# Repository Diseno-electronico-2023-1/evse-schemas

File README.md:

# evse-schemas

Cada grupo crea una rama para su PCB, cuando acaben hacen merge a la rama

Para crear una rama:

git checkout -b branch-name

Donde branch-name es el nombre de la rama Ej: Potencia

Una vez que estan en la nueva rama pueden subir sus cambios con:

git add .

git commit -m "Descripción de sus cambios"

git push -u origin branch-name

## Table of Contents
- [Conector](#conector)
- [Control Pilot](#controlPilot)

## CONECTOR
### Pruebas
#### Tension
Para esta prueba se realiza un montaje en paralelo entre una linea y neutro del conector con una fuente de tensión en AC, Como se observa en el siguiente montaje.

Se realiza la respectiva verificación de la tensión a la que estará expuesto el conector y se realizan distintas pruebas con diferentes valores de voltaje obteniendo los siguientes resultados.

#### Corriente
En esta prueba se conecto en serie una fuente de corriente como se muestra en la siguiente figura.

Se inicio la medicion con 5 A y posteriormente se aumento a los 15 A que están propuestos para el cargador y con la ayuda de una pinza amperimétrica y un osciloscopio se observaron las corrientes suministradas en una escala de 10mV por cada amperio.

#### Aislamiento
Para determinar la resistencia de aislamiento del conector se utiliza un medidor de resistencia de aislamiento, con los cables aislados entre si se conectan a una linea y al neutro del conector como se observa el montaje en la siguiente figura. La resistencia obtenida fue de 319 Gohm. 

Comparando este valor con el dado comercialmente se obtiene una resistencia considerablemente mayor a la descrita en el manual.

<div align="center">

Votaje [RMS]  | Corriente [A] | Aislamiento [Gomh]
------------- | ------------- | -------------
121  | 5  | 319
383  | 15 
447  | 16
</div>

## CONTROL PILOT
El circuito piloto de control es el principal medio de control para garantizar un funcionamiento correcto al conectar un EV/PHEV al EVSE. La señal piloto es el método clave a través del cual un EVSE compatible con J1772 se comunica con un vehículo. La señal piloto se basa en una señal PWM de ±12 V y 1 kHz que se transmite a un vehículo a través del cable de carga. El vehículo puede entonces responder colocando diversas cargas en la línea, afectando a su tensión, que mide el EVSE.
El protocolo de señalización ha sido diseñado para la siguiente secuencia de carga.

- El equipo de alimentación señala la presencia de alimentación de entrada de CA
- El vehículo detecta el enchufe mediante un circuito de proximidad (de este modo, el vehículo puede evitar alejarse mientras está conectado) y puede detectar cuando se pulsa el pestillo para preparar la extracción del enchufe.

Comienzan las funciones del piloto de control (CP)

- El equipo de alimentación detecta el vehículo eléctrico enchufable (PEV)
- El equipo de suministro indica al PEV que está preparado para suministrar corriente
- Se determinan las necesidades de ventilación del PEV
- el equipo de alimentación suministra corriente al PEV
- El PEV ordena el flujo de energía
- El PEV y el equipo de alimentación supervisan continuamente la continuidad de la toma de tierra de seguridad
- La carga continúa según lo determinado por el PEV
- La carga puede interrumpirse desconectando el enchufe del vehículo

Esta seccion esta basado en la plantilla [Conector](https://github.com/Diseno-electronico-2023-1/evse-schemas/tree/Conector/Conector "Conector")

### Control Pilot - simulación
Este apartado tiene como carpeta principal [Simulación](https://github.com/Diseno-electronico-2023-1/evse-schemas/tree/Conector/Conector/Simulacion)

#### Table SAE J1772 - PILOT SIGNAL
<div align="center">
                    
Designación del estado del vehículo  |Voltaje (VDC nominal) | Descripción del estado del vehículo
------------- | ------------- | -------------
Estado A  | 12 | Vehículo no conectado
Estado B  | 9 | Vehículo conectado / no está listo para aceptar energía
Estado C  | 6 | Vehículo conectado / listo para aceptar energía / no se requiere ventilación en el área de carga interna
Estado D  | 3 | Vehículo conectado / listo para aceptar energía /requiere ventilación en el área de carga interna
Estado E  | 0 | EVSE desconectado, poder de utilidad no disponible, u otro problema de EVSE
Estado F  | -12 | EVSE no disponible, u otro problema de EVSE
</div>

1. El EVSE pone 12V en el cable piloto. Esta transmisión señala al vehículo cuando el enchufe está conectado.
2. Cuando se conecta el enchufe, el vehículo coloca una carga de 2,74 kΩ en la línea piloto, lo que disminuye la tensión a 9 V.
3. La EVSE pasa al estado B, donde activa el PWM, que indica al vehículo cuánta corriente puede consumir. El EVSE también cierra los relés, proporcionando energía al vehículo.
4. El vehículo comienza a consumir energía y cambia a la carga de 822-Ω, que baja la tensión a 6 V, señalando al EVSE que la carga ha comenzado.
5. La mayoría de los vehículos siguen consumiendo pequeñas cantidades de energía en el estado C, incluso cuando están completamente cargados, por lo que el proceso de carga finaliza desenchufando el cable, lo que devuelve la tensión a 12 V. El EVSE mide este proceso y cierra los relés y vuelve al estado A.

#### J1772 Ciclo de trabajo

El ciclo de trabajo de las señales piloto comunica el límite de corriente que el EVSE es capaz de suministrar al vehículo; el vehículo puede entonces utilizar hasta esa cantidad de corriente para su circuito de carga. Este límite de corriente viene determinada principalmente por los componentes electromecánicos de la EVSE, como conductores, relés contactores y la conexión de servicio. La relación entre el ciclo de trabajo y la corriente se define mediante dos ecuaciones diferentes en función del rango de corriente especificado.

Rango de corriente especificado; para un servicio de 6 a 51 A, es:
Duty Cycle = Amps / 0.6

<div align="center">

AMPS  | DUTY CYCLE
------------- | -------------
5  | 8.3%
15  | 25% 
30  | 50%
40  | 66.6%
65  | 90%
80  | 96%
</div>

### Control Pilot - PCB
Esta subseccion esta basado en la plantilla [PCB](https://github.com/Diseno-electronico-2023-1/evse-schemas/tree/Conector/Conector/ControlPilotPCB-backups)

<p align="center">

</p>

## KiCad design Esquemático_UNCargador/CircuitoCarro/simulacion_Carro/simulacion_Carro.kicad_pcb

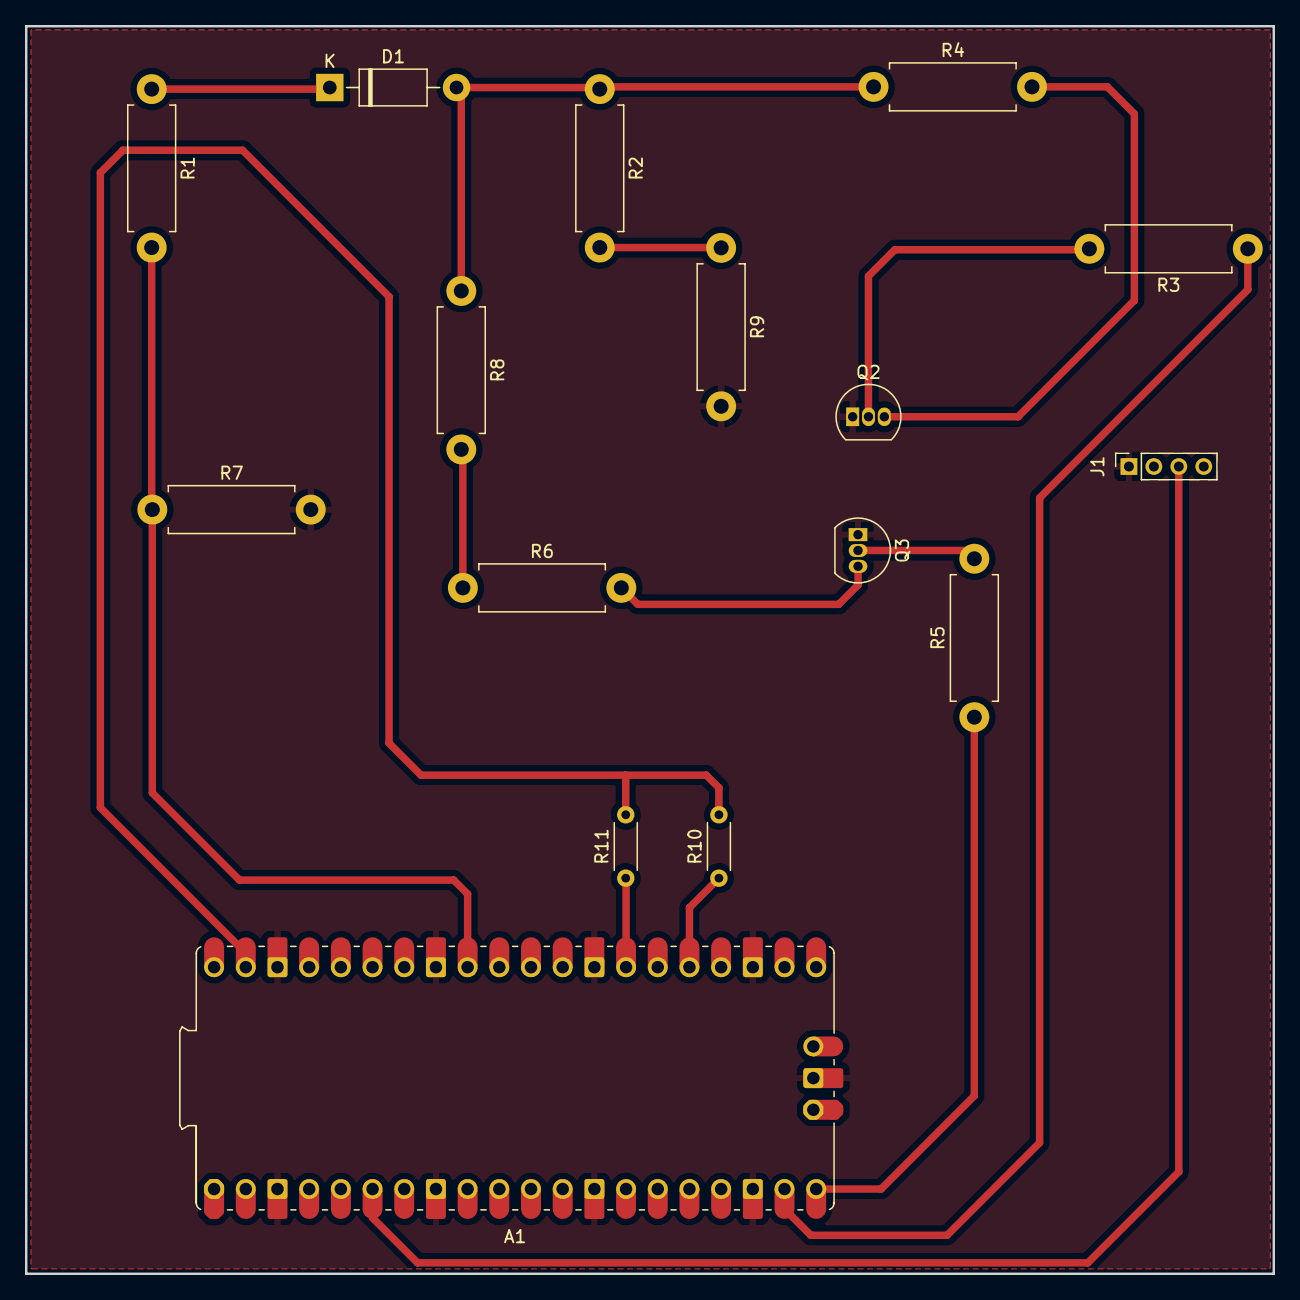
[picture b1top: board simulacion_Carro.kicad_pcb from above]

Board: 2 copper layers, 100.0 x 100.0 mm, 16 parts (0 on the bottom side), 16 nets.

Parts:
A1: RaspberryPi-Pico; Raspberry_Pi_Pico_SMT_THT
D1: 1N4004; D_DO-41_SOD81_P10.16mm_Horizontal
J1: Conn_01x04_Pin; PinSocket_1x04_P2.00mm_Vertical
Q2, Q3: 2N2222; TO-92_Inline
R1: 90k; R_Axial_DIN0411_L9.9mm_D3.6mm_P12.70mm_Horizontal
R2: 2.7k; R_Axial_DIN0411_L9.9mm_D3.6mm_P12.70mm_Horizontal
R3, R5: 1k; R_Axial_DIN0411_L9.9mm_D3.6mm_P12.70mm_Horizontal
R4: 330; R_Axial_DIN0411_L9.9mm_D3.6mm_P12.70mm_Horizontal
R6: 1.2k; R_Axial_DIN0411_L9.9mm_D3.6mm_P12.70mm_Horizontal
R7: 10k; R_Axial_DIN0411_L9.9mm_D3.6mm_P12.70mm_Horizontal
R8: 100; R_Axial_DIN0411_L9.9mm_D3.6mm_P12.70mm_Horizontal
R9: 39; R_Axial_DIN0411_L9.9mm_D3.6mm_P12.70mm_Horizontal
R10, R11: R; R_Axial_DIN0204_L3.6mm_D1.6mm_P5.08mm_Horizontal

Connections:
+5V: A1.39 (VSYS), R10.2, R11.2
/micro/pilot_micro: A1.32 (GPIO27_ADC1), R1.2, R7.1
/micro/pwm1: A1.19 (GPIO14), R3.1
/micro/pwm2: A1.20 (GPIO15), R5.1
GND: A1.3 (GND), A1.8 (GND), A1.13 (GND), A1.18 (GND), A1.23 (GND), A1.28 (GND), A1.33 (AGND), A1.38 (GND), A1.42 (SWGND), J1.1, Q2.1 (E), Q3.1 (E), R7.2, R9.2
unnamed: A1.25 (GPIO19), R10.1
unnamed: A1.27 (GPIO21), R11.1
unnamed: D1.1 (K), R1.1
unnamed: Q2.2 (B), R3.2
unnamed: Q2.3 (C), R4.2
unnamed: Q3.2 (B), R5.2
unnamed: Q3.3 (C), R6.2
unnamed: R2.2, R9.1
unnamed: R6.1, R8.2
SDA: A1.6 (GPIO4), J1.3
pilot_in_carg: D1.2 (A), R2.1, R4.1, R8.1

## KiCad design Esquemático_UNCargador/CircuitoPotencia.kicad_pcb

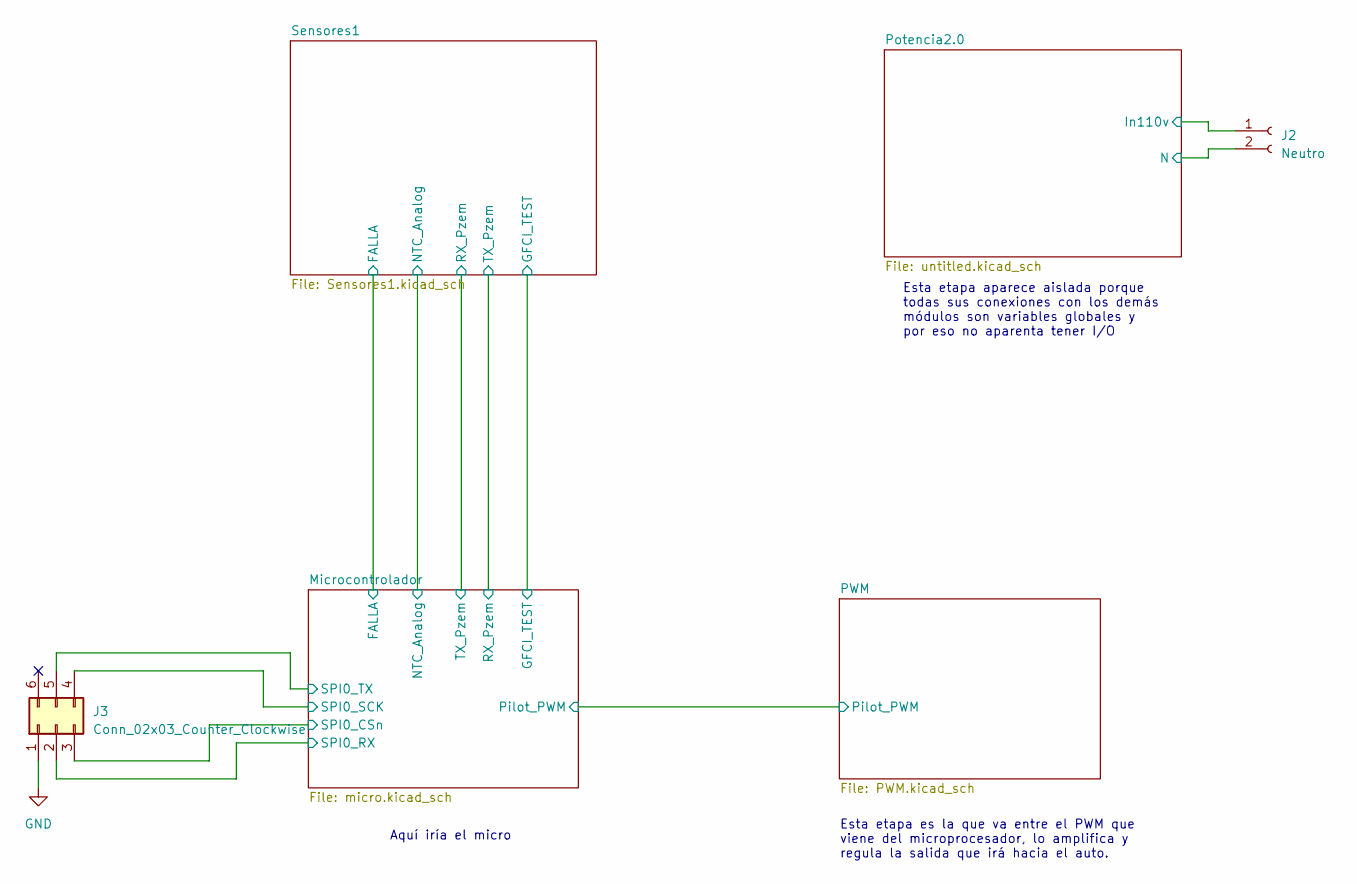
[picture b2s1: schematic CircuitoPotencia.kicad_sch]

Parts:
J2: Neutro; TerminalBlock_Wuerth_691311400102_P7.62mm
J3: Conn_02x03_Counter_Clockwise; IDC-Header_2x05_P2.54mm_Vertical

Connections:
/Microcontrolador/SPI0_CSn: J3.3; also elsewhere on the board
/Microcontrolador/SPI0_RX: J3.2; also elsewhere on the board
/Microcontrolador/SPI0_SCK: J3.4; also elsewhere on the board
/Microcontrolador/SPI0_TX: J3.5; also elsewhere on the board
unnamed 21: J2.2; also elsewhere on the board
unnamed 22: J2.1; also elsewhere on the board

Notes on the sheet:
Aquí iría el micro
Esta etapa es la que va entre el PWM que viene del microprocesador, lo amplifica y regula la salida que irá hacia el auto.
Esta etapa aparece aislada porque todas sus conexiones con los demás módulos son variables globales y por eso no aparenta tener I/O

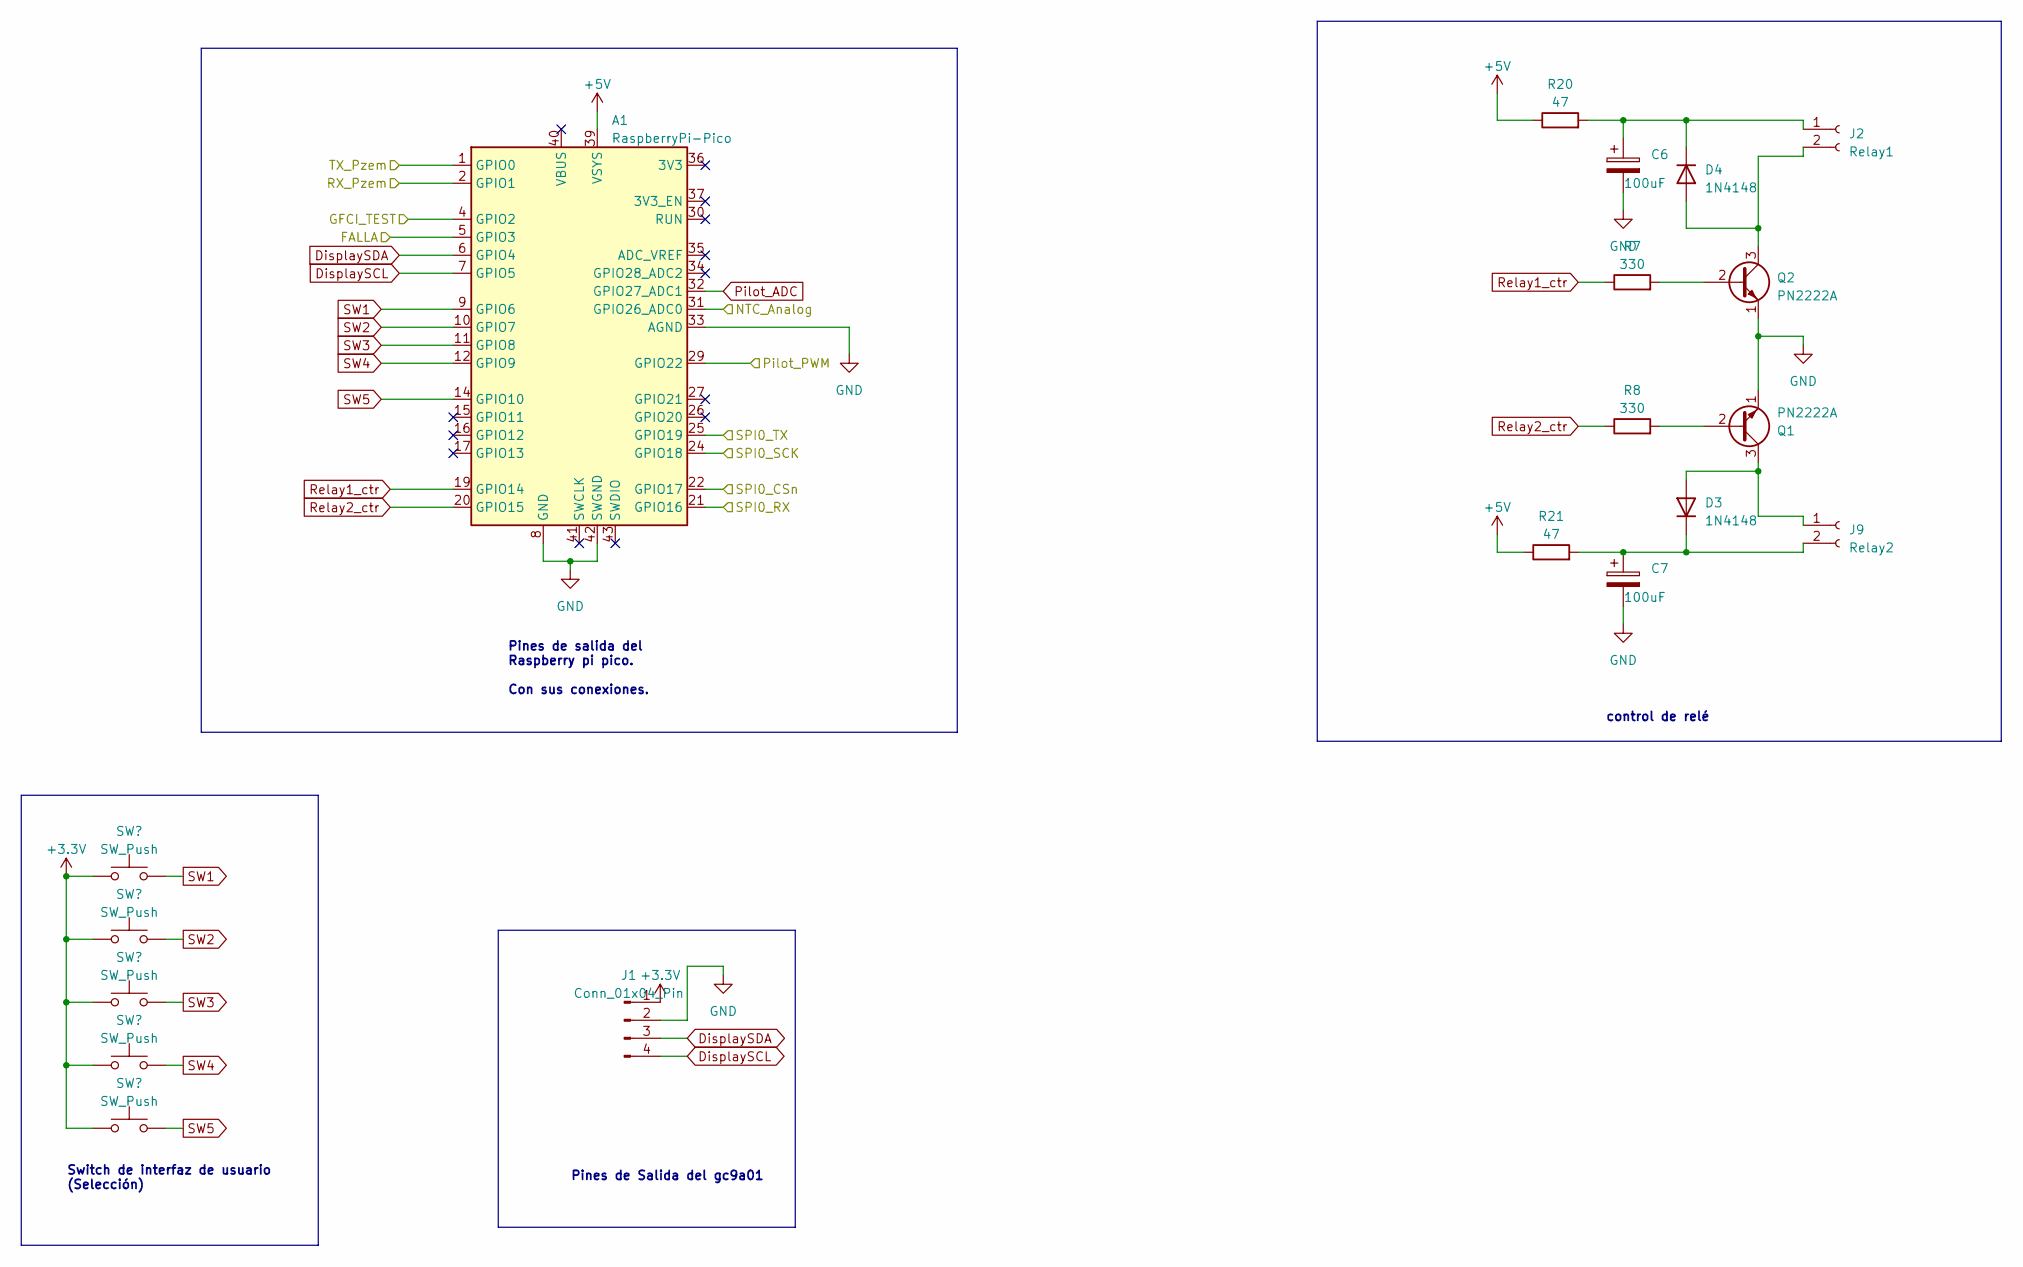
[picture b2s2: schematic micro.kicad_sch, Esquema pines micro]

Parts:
A1: RaspberryPi-Pico; Raspberry_Pi_Pico_SMT_THT
C6, C7: 100uF; CP_Radial_D8.0mm_P3.50mm
D3, D4: 1N4148; D_DO-35_SOD27_P7.62mm_Horizontal
J1: Conn_01x04_Pin; PinHeader_1x04_P2.54mm_Vertical
J2: Relay1; Molex_KK-254_AE-6410-02A_1x02_P2.54mm_Vertical
J9: Relay2; Molex_KK-254_AE-6410-02A_1x02_P2.54mm_Vertical
Q1, Q2: PN2222A; TO-92_Inline
R7, R8: 330; R_Axial_DIN0207_L6.3mm_D2.5mm_P10.16mm_Horizontal
R20, R21: 47; R_Axial_DIN0207_L6.3mm_D2.5mm_P10.16mm_Horizontal
SW1, SW2, SW3, SW4, SW5: SW_Push; PinHeader_1x02_P2.54mm_Vertical

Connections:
+3.3V: J1.1, SW1.1, SW2.1, SW3.1, SW4.1, SW5.1; also elsewhere on the board
+5V: A1.39 (VSYS), R20.1, R21.1; also elsewhere on the board
/Microcontrolador/FALLA: A1.5 (GPIO3); also elsewhere on the board
/Microcontrolador/GFCI_TEST: A1.4 (GPIO2); also elsewhere on the board
/Microcontrolador/NTC_Analog: A1.31 (GPIO26_ADC0); also elsewhere on the board
/Microcontrolador/Pilot_PWM: A1.29 (GPIO22); also elsewhere on the board
/Microcontrolador/RX_Pzem: A1.2 (GPIO1); also elsewhere on the board
/Microcontrolador/SPI0_CSn: A1.22 (GPIO17); also elsewhere on the board
/Microcontrolador/SPI0_RX: A1.21 (GPIO16); also elsewhere on the board
/Microcontrolador/SPI0_SCK: A1.24 (GPIO18); also elsewhere on the board
/Microcontrolador/SPI0_TX: A1.25 (GPIO19); also elsewhere on the board
/Microcontrolador/TX_Pzem: A1.1 (GPIO0); also elsewhere on the board
DisplaySCL: A1.7 (GPIO5), J1.4
DisplaySDA: A1.6 (GPIO4), J1.3
unnamed: D3.2 (A), J9.1, Q1.3 (C)
unnamed: C7.1, D3.1 (K), J9.2, R21.2
unnamed: D4.2 (A), J2.2, Q2.3 (C)
unnamed: C6.1, D4.1 (K), J2.1, R20.2
unnamed: Q1.2 (B), R8.2
unnamed: Q2.2 (B), R7.2
Pilot_ADC: A1.32 (GPIO27_ADC1); also elsewhere on the board
Relay1_ctr: A1.19 (GPIO14), R7.1
Relay2_ctr: A1.20 (GPIO15), R8.1
SW1: A1.9 (GPIO6), SW1.2
SW2: A1.10 (GPIO7), SW2.2
SW3: A1.11 (GPIO8), SW3.2
SW4: A1.12 (GPIO9), SW4.2
SW5: A1.14 (GPIO10), SW5.2

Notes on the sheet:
Pines de salida del Raspberry pi pico. Con sus conexiones.
control de relé
Switch de interfaz de usuario (Selección)
Pines de Salida del gc9a01

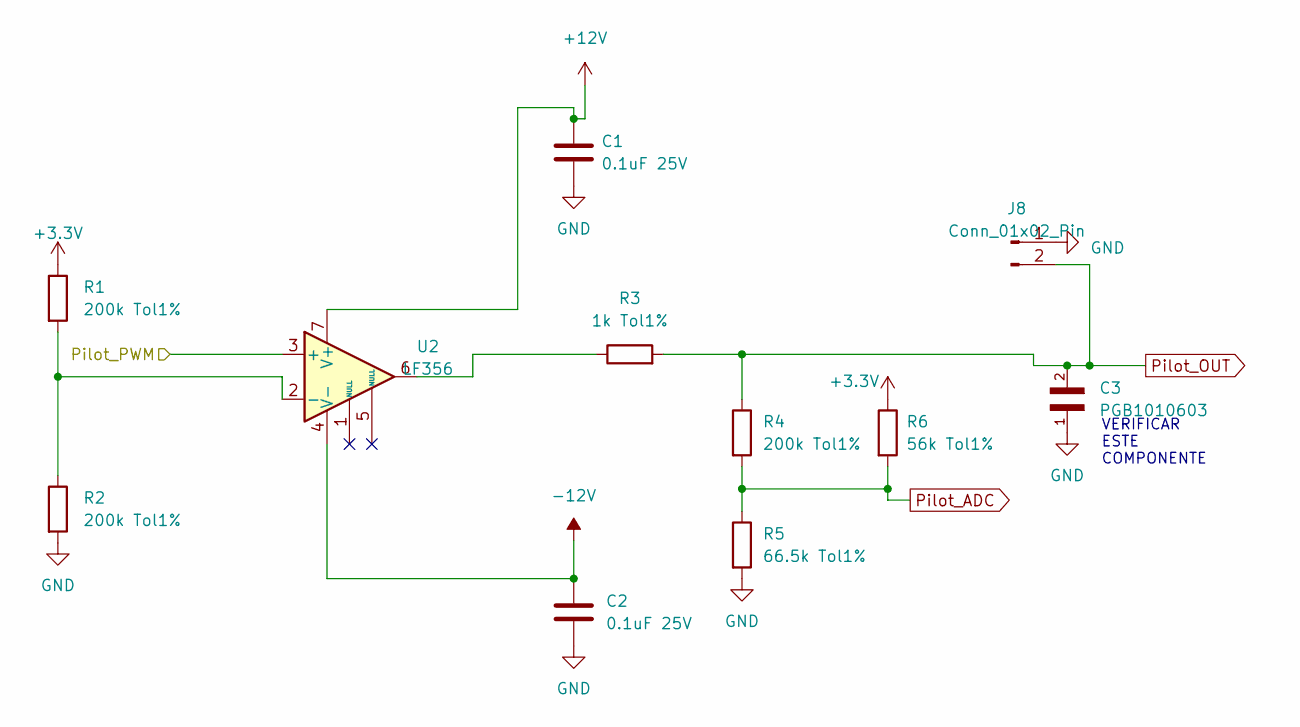
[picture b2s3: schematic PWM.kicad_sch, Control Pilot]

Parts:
C1, C2: 0.1uF 25V; CP_Radial_D4.0mm_P1.50mm
C3: PGB1010603; R_0603_1608Metric_Pad0.98x0.95mm_HandSolder
J8: Conn_01x02_Pin; TerminalBlock_Wuerth_691311400102_P7.62mm
R1, R2, R4: 200k Tol1%; R_Axial_DIN0204_L3.6mm_D1.6mm_P5.08mm_Horizontal
R3: 1k Tol1%; R_Axial_DIN0204_L3.6mm_D1.6mm_P5.08mm_Horizontal
R5: 66.5k Tol1%; R_Axial_DIN0204_L3.6mm_D1.6mm_P5.08mm_Horizontal
R6: 56k Tol1%; R_Axial_DIN0204_L3.6mm_D1.6mm_P5.08mm_Horizontal
U2: LF356; DIL08

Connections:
+3.3V: R1.1, R6.1; also elsewhere on the board
+12V: C1.1, U2.7 (V+); also elsewhere on the board
-12V: C2.1, U2.4 (V-); also elsewhere on the board
/Microcontrolador/Pilot_PWM: U2.3 (+); also elsewhere on the board
unnamed: R3.1, U2.6
unnamed: R1.2, R2.1, U2.2 (-)
Pilot_ADC: R4.2, R5.1, R6.2; also elsewhere on the board
Pilot_OUT: C3.2, J8.2, R3.2, R4.1

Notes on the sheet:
VERIFICAR ESTE COMPONENTE

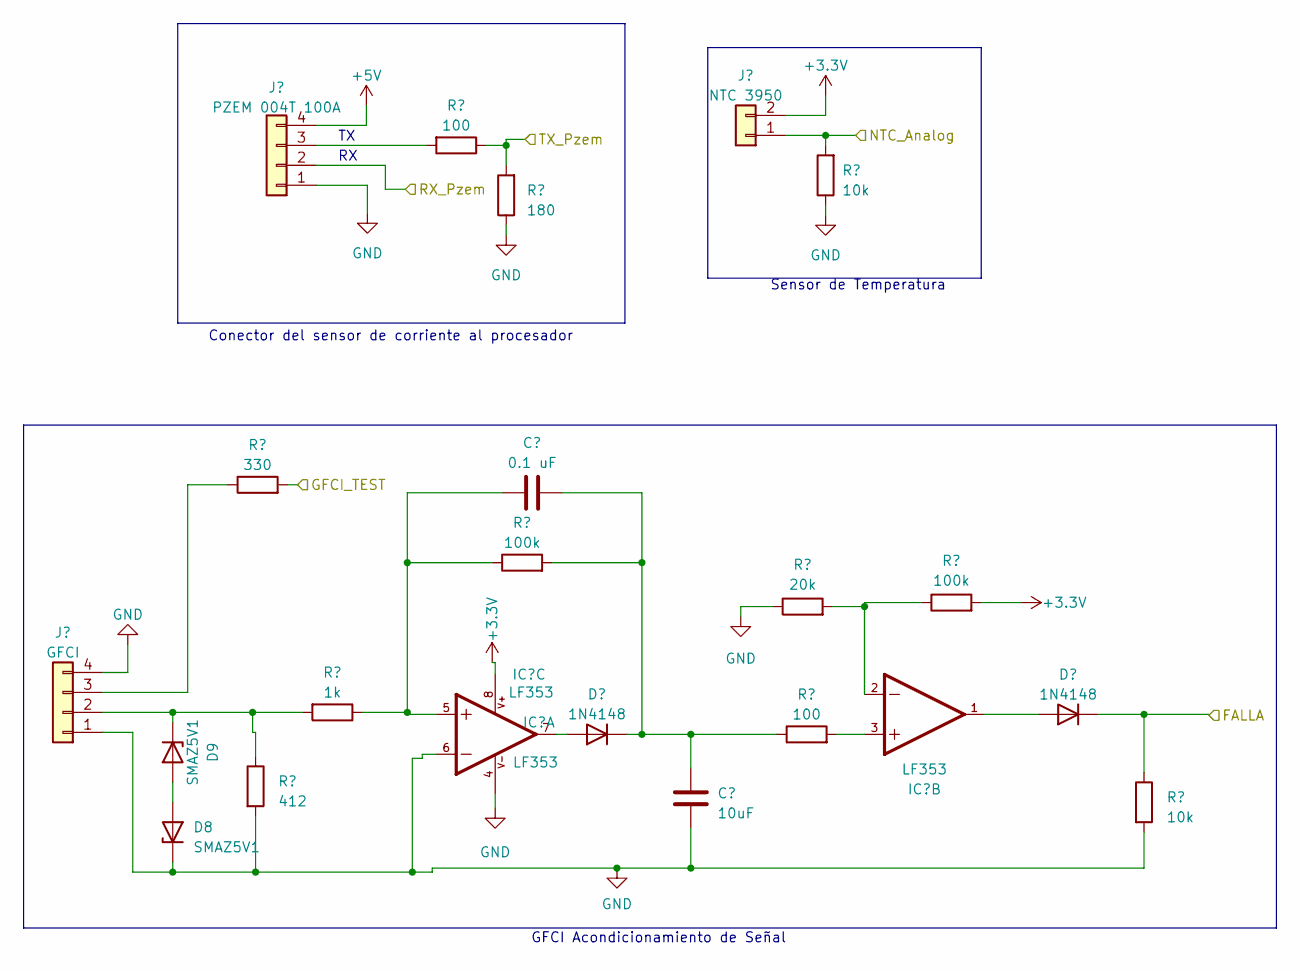
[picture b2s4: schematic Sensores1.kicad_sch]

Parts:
C4: 0.1 uF; C_0805_2012Metric_Pad1.18x1.45mm_HandSolder
C5: 10uF; C_0805_2012Metric_Pad1.18x1.45mm_HandSolder
D5, D6: 1N4148; D_DO-35_SOD27_P7.62mm_Horizontal
D8, D9: SMAZ5V1; DO-214AC
IC1: LF353; DIL08
J4: GFCI; JST_EH_B4B-EH-A_1x04_P2.50mm_Vertical
J5: PZEM 004T 100A; PZEM
J6: NTC 3950; JST_EH_B2B-EH-A_1x02_P2.50mm_Vertical
R9: 412; R_1206_3216Metric_Pad1.30x1.75mm_HandSolder
R10: 330; R_1206_3216Metric_Pad1.30x1.75mm_HandSolder
R11: 1k; R_1206_3216Metric_Pad1.30x1.75mm_HandSolder
R12, R16: 100; R_1206_3216Metric_Pad1.30x1.75mm_HandSolder
R13: 180; R_1206_3216Metric_Pad1.30x1.75mm_HandSolder
R14, R18: 100k; R_1206_3216Metric_Pad1.30x1.75mm_HandSolder
R15: 20k; R_1206_3216Metric_Pad1.30x1.75mm_HandSolder
R17, R19: 10k; R_1206_3216Metric_Pad1.30x1.75mm_HandSolder

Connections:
+3.3V: IC1.8, J6.2, R18.2; also elsewhere on the board
+5V: J5.4; also elsewhere on the board
/Microcontrolador/FALLA: D6.1 (K), R19.1; also elsewhere on the board
/Microcontrolador/GFCI_TEST: R10.2; also elsewhere on the board
/Microcontrolador/NTC_Analog: J6.1, R17.2; also elsewhere on the board
/Microcontrolador/RX_Pzem: R12.1, R13.2; also elsewhere on the board
/Microcontrolador/TX_Pzem: J5.2; also elsewhere on the board
unnamed: C4.1, IC1.5, R11.1, R14.1
unnamed: D5.2 (A), IC1.7
unnamed: C4.2, C5.1, D5.1 (K), R14.2, R16.1
unnamed: D6.2 (A), IC1.1
unnamed: D8.2 (A), D9.2 (A)
unnamed: D9.1 (K), J4.2, R9.1, R11.2
unnamed: IC1.2, R15.2, R18.1
unnamed: IC1.3, R16.2
unnamed: J4.3, R10.1
unnamed: J5.3, R12.2

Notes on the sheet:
Conector del sensor de corriente al procesador
GFCI Acondicionamiento de Señal
Sensor de Temperatura

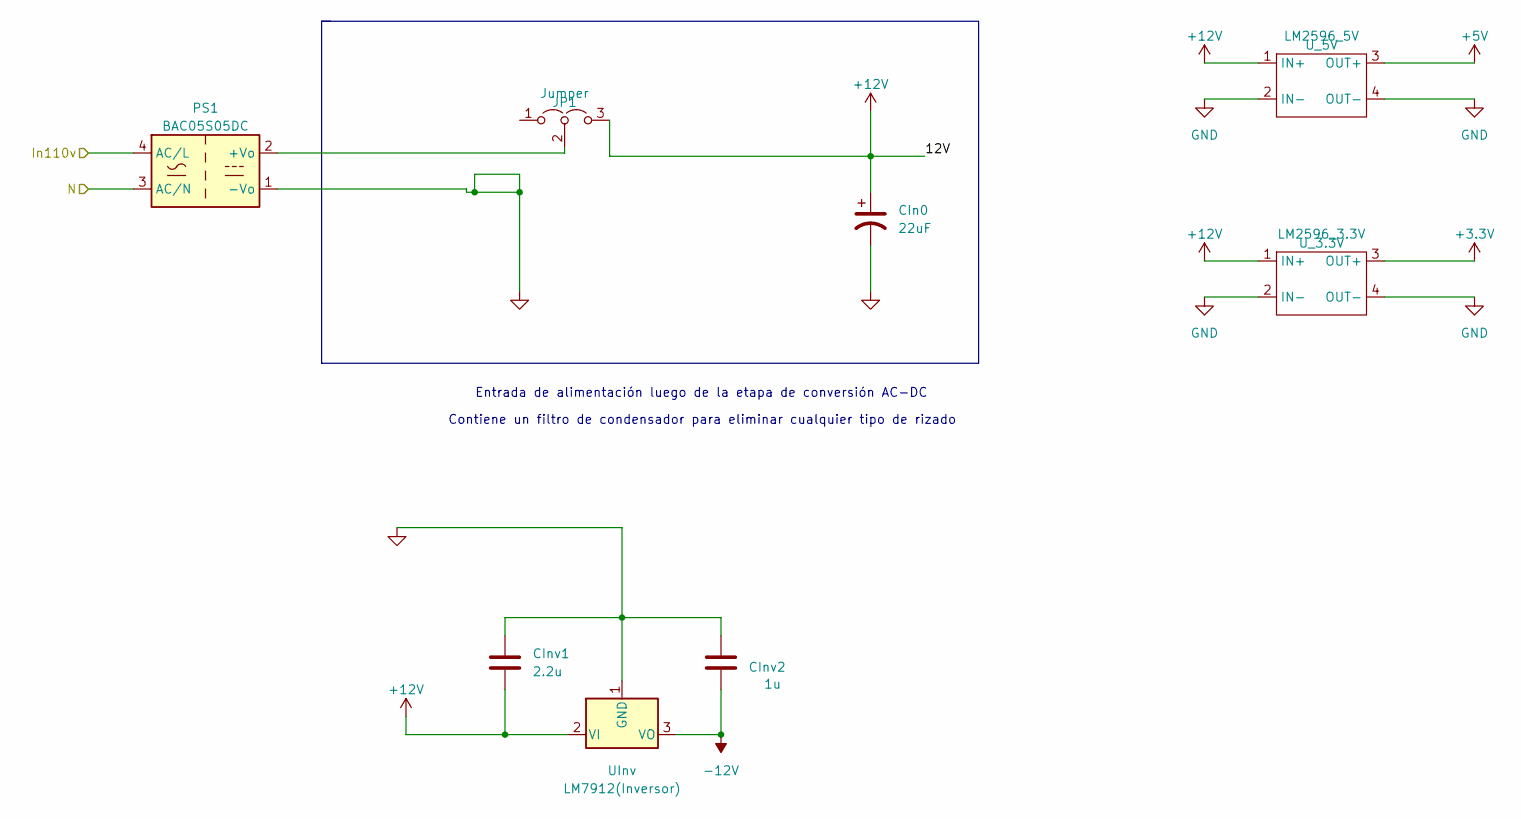
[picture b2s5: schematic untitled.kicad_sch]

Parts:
CIn0: 22uF; C_0805_2012Metric_Pad1.18x1.45mm_HandSolder
CInv1: 2.2u; C_Radial_D10.0mm_H16.0mm_P5.00mm
CInv2: 1u; C_Radial_D10.0mm_H16.0mm_P5.00mm
JP1: Jumper; PinHeader_1x03_P2.54mm_Vertical
PS1: BAC05S05DC; AC-DC_Converter
UInv: LM7912(Inversor); TO-220-3_Vertical
U_3.3V: LM2596_3.3V; LM2596ADJ
U_5V: LM2596_5V; LM2596ADJ

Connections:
+12V: CIn0.1, JP1.3 (B); also elsewhere on the board
unnamed 32: JP1.2 (C); also elsewhere on the board

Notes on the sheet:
Entrada de alimentación luego de la etapa de conversión AC-DC
Contiene un filtro de condensador para eliminar cualquier tipo de rizado

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
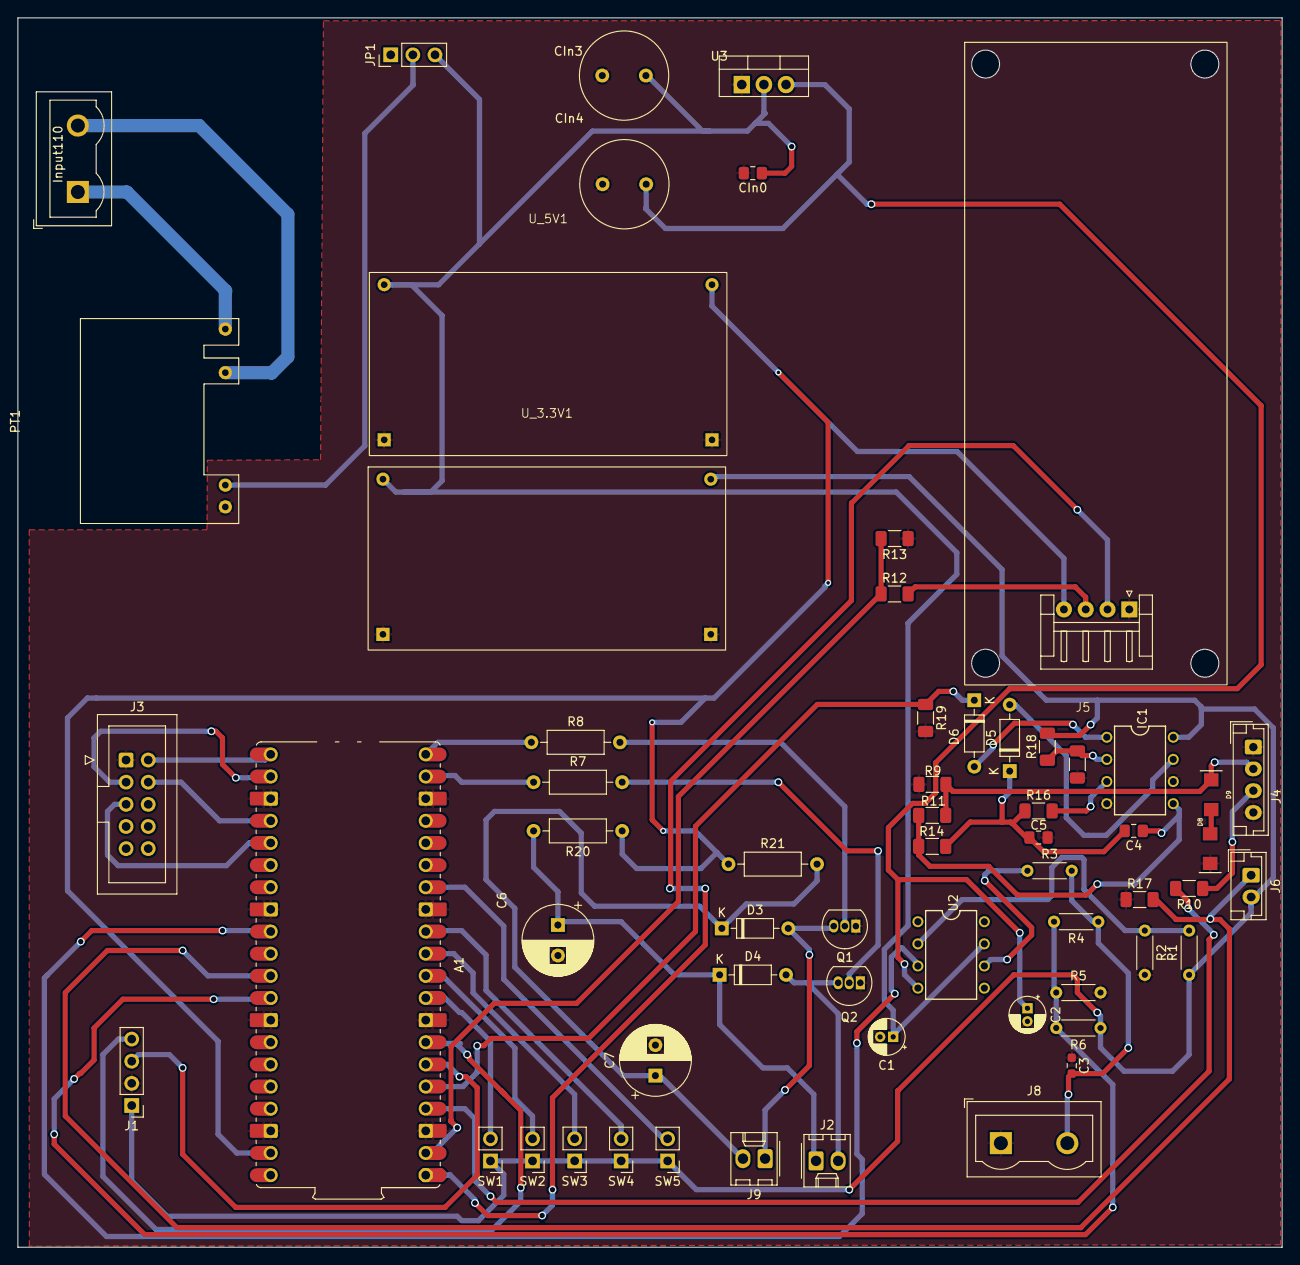
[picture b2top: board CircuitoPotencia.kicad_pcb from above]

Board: 2 copper layers, 145.0 x 141.0 mm, 61 parts (0 on the bottom side), 47 nets.

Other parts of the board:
CIn3: 2.2u; C_Radial_D10.0mm_H16.0mm_P5.00mm
CIn4: 1u; C_Radial_D10.0mm_H16.0mm_P5.00mm
Input110: Neutro; TerminalBlock_Wuerth_691311400102_P7.62mm
PT1: BAC05S05DC; AC-DC_Converter
U3: LM7912(Inversor); TO-220-3_Vertical
U_3.3V1: LM2596_3.3V; LM2596ADJ
U_5V1: LM2596_5V; LM2596ADJ

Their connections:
+3.3V: U_3.3V1.3 (OUT+); also elsewhere on the board
+5V: U_5V1.3 (OUT+); also elsewhere on the board
+12V: CIn3.2, U3.2 (VI), U_3.3V1.1 (IN+), U_5V1.1 (IN+); also elsewhere on the board
-12V: CIn4.2, U3.3 (VO); also elsewhere on the board
/Potencia2.0/In110v: Input110.1, PT1.4 (AC/L)
/Potencia2.0/N: Input110.2, PT1.3 (AC/N)
unnamed 32: PT1.2 (+Vo); also elsewhere on the board

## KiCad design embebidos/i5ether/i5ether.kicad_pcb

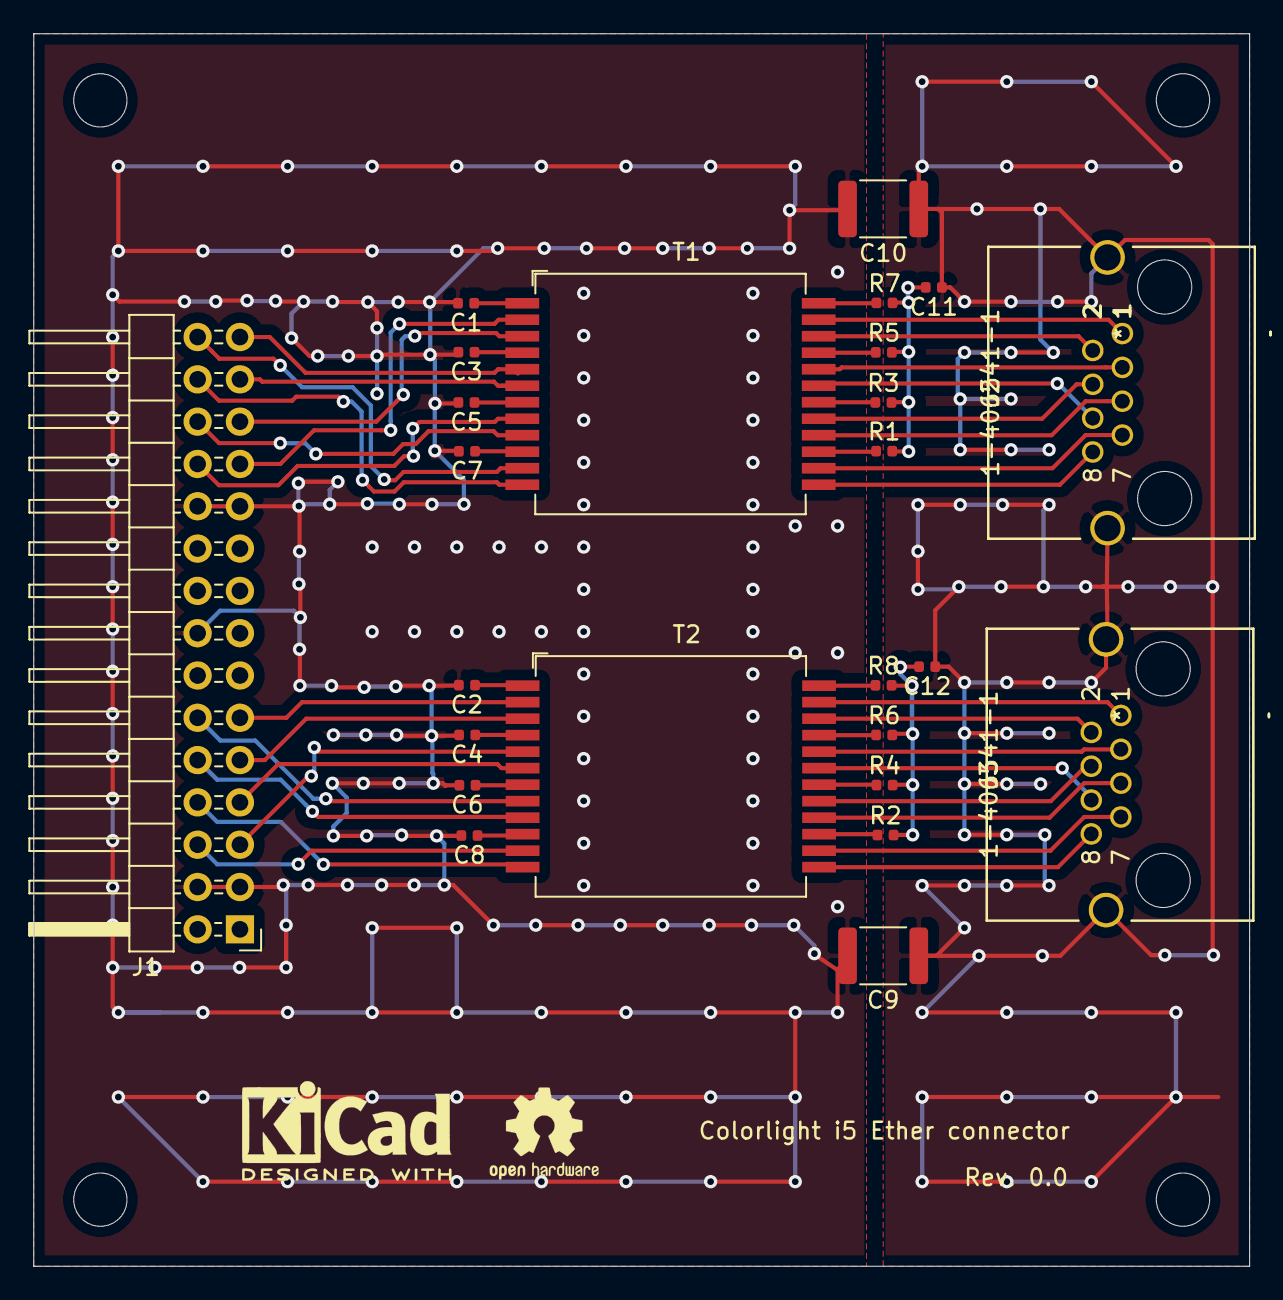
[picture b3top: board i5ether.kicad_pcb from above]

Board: 2 copper layers, 73.0 x 74.0 mm, 25 parts (0 on the bottom side), 52 nets.

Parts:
C1, C2, C3, C4, C5, C6, C7, C8: 0.1u; C_0402_1005Metric
C9, C10: 4700p; R_1812_4532Metric
C11, C12: 1000p; C_0402_1005Metric
J1: Conn_02x15_Odd_Even; PinHeader_2x15_P2.54mm_Horizontal
J2, J3: 1-406541-1
R1, R2, R3, R4, R5, R6, R7, R8: 75; R_0402_1005Metric
T1, T2: HX5008; HX5008NL

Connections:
Earth: C9.1, C10.1, C11.1, C12.1, J2.9, J2.10, J3.9, J3.10
GND: C1.2, C2.2, C3.2, C4.2, C5.2, C6.2, C7.2, C8.2, C9.2, C10.2, J1.3, J1.4, J1.16, J1.21, J1.22
unnamed: C1.1, T1.1
unnamed: C2.1, T2.1
unnamed: C3.1, T1.4
unnamed: C4.1, T2.4
unnamed: C5.1, T1.7
unnamed: C6.1, T2.7
unnamed: C7.1, T1.10
unnamed: C8.1, T2.10
unnamed: C11.2, R1.2, R3.2, R5.2, R7.2
unnamed: C12.2, R2.2, R4.2, R6.2, R8.2
unnamed: J1.5, T2.5
unnamed: J1.6, T2.11
unnamed: J1.7, T2.6
unnamed: J1.8, T2.12
unnamed: J1.9, T2.3
unnamed: J1.10, T2.9
unnamed: J1.11, T2.2
unnamed: J1.12, T2.8
unnamed: J1.23, T1.2
unnamed: J1.24, T1.8
unnamed: J1.25, T1.3
unnamed: J1.26, T1.9
unnamed: J1.27, T1.6
unnamed: J1.28, T1.12
unnamed: J1.29, T1.5
unnamed: J1.30, T1.11
unnamed: J2.1, T1.23
unnamed: J2.2, T1.22
unnamed: J2.3, T1.20
unnamed: J2.4, T1.17
unnamed: J2.5, T1.16
unnamed: J2.6, T1.19
unnamed: J2.7, T1.14
unnamed: J2.8, T1.13
unnamed: J3.1, T2.23
unnamed: J3.2, T2.22
unnamed: J3.3, T2.20
unnamed: J3.4, T2.17
unnamed: J3.5, T2.16
unnamed: J3.6, T2.19
unnamed: J3.7, T2.14
unnamed: J3.8, T2.13
unnamed: R1.1, T1.15
unnamed: R2.1, T2.15
unnamed: R3.1, T1.18
unnamed: R4.1, T2.18
unnamed: R5.1, T1.21
unnamed: R6.1, T2.21
unnamed: R7.1, T1.24
unnamed: R8.1, T2.24

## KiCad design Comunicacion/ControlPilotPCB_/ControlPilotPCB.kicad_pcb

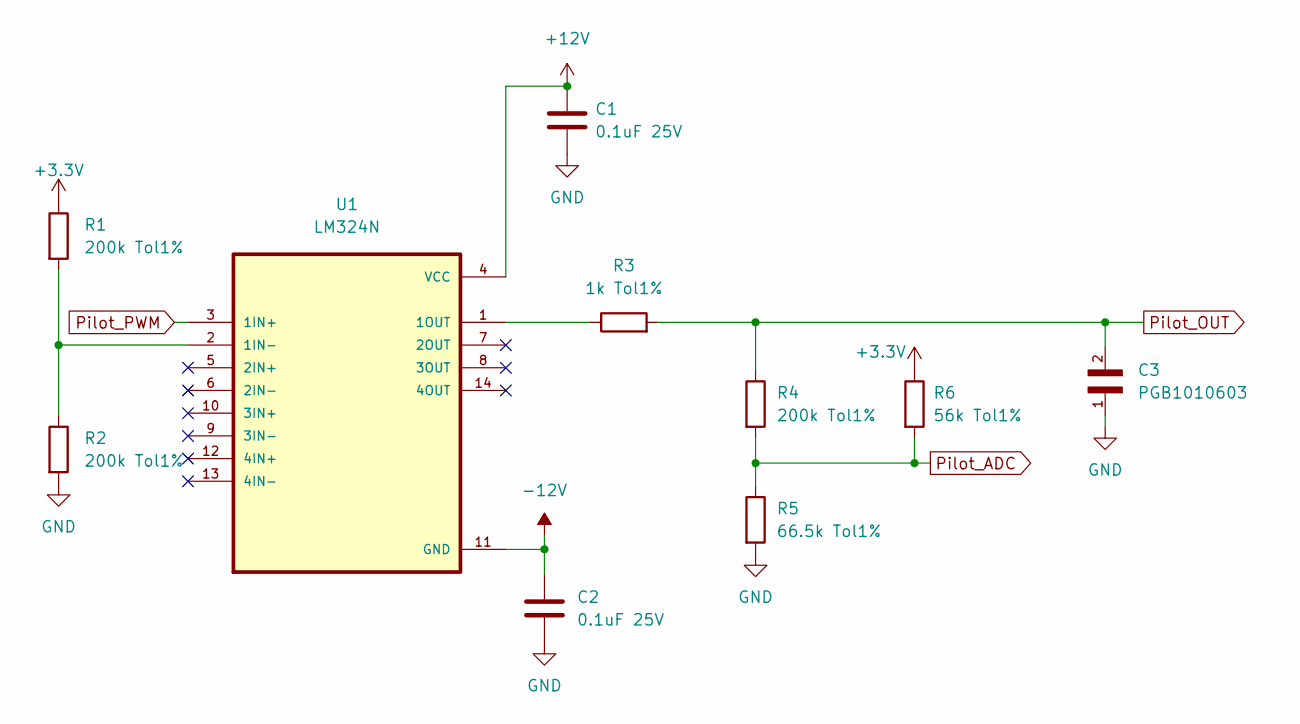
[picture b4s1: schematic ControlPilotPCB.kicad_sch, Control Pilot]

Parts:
C1, C2: 0.1uF 25V; CP_Radial_D4.0mm_P1.50mm
C3: PGB1010603; ESD_PGB1010603MR
R1, R2, R4: 200k Tol1%; R_Axial_DIN0204_L3.6mm_D1.6mm_P5.08mm_Horizontal
R3: 1k Tol1%; R_Axial_DIN0204_L3.6mm_D1.6mm_P5.08mm_Horizontal
R5: 66.5k Tol1%; R_Axial_DIN0204_L3.6mm_D1.6mm_P5.08mm_Horizontal
R6: 56k Tol1%; R_Axial_DIN0204_L3.6mm_D1.6mm_P5.08mm_Horizontal
U1: LM324N; DIP794W45P254L1969H508Q14

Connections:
+3.3V: R1.1, R6.1
+12V: C1.1, U1.4 (VCC)
-12V: C2.1, U1.11 (GND)
GND: C1.2, C2.2, C3.1, R2.2, R5.2
unnamed: R1.2, R2.1, U1.2 (1IN-)
unnamed: R3.1, U1.1 (1OUT)
Pilot_ADC: R4.2, R5.1, R6.2
Pilot_OUT: C3.2, R3.2, R4.1
Pilot_PWM: U1.3 (1IN+)

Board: 2 copper layers, 10 parts (0 on the bottom side), 8 nets, no tracks yet.

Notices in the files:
parts and their libraries:
Copyright 2016 Accelerated Designs. All rights reserved.
